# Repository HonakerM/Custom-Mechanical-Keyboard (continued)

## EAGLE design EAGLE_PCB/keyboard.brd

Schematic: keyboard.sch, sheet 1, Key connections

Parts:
0, 1, 2, 3, 4, 5, 6, 7, 8, 9: KEYSWITCH-RGBSMDLED-ALPSMX-1U-SMDRGB; ALPSMX-1U-SMDRGB
A: KEYSWITCH-RGBSMDLED-ALPSMX-1U-SMDRGB; ALPSMX-1U-SMDRGB
ALT, ALT2: KEYSWITCH-RGBSMDLED-ALPSMX-1U-SMDRGB; ALPSMX-1U-SMDRGB
B: KEYSWITCH-RGBSMDLED-ALPSMX-1U-SMDRGB; ALPSMX-1U-SMDRGB
BACKSLASH: KEYSWITCH-RGBSMDLED-ALPSMX-1U-SMDRGB; ALPSMX-1U-SMDRGB
BACKSONG: KEYSWITCH-RGBSMDLED-ALPSMX-1U-SMDRGB; ALPSMX-1U-SMDRGB
BACKSPACE: KEYSWITCH-RGBSMDLED-ALPSMX-2U-SMDRGB; ALPSMX-2U-SMDRGB
BACKSPACE_1: KEYSWITCH-RGBSMDLED-ALPSMX-1U-SMDRGB; ALPSMX-1U-SMDRGB
C: KEYSWITCH-RGBSMDLED-ALPSMX-1U-SMDRGB; ALPSMX-1U-SMDRGB
CAPSLOCK: KEYSWITCH-RGBSMDLED-ALPSMX-1U-SMDRGB; ALPSMX-1U-SMDRGB
COMMA: KEYSWITCH-RGBSMDLED-ALPSMX-1U-SMDRGB; ALPSMX-1U-SMDRGB
CTRL, CTRL1, CTRL2: KEYSWITCH-RGBSMDLED-ALPSMX-1U-SMDRGB; ALPSMX-1U-SMDRGB
D: KEYSWITCH-RGBSMDLED-ALPSMX-1U-SMDRGB; ALPSMX-1U-SMDRGB
D0, D1, D2, D3, D4, D5, D6, D7, D8, D9: DIODE-SOD-123; SOD-123
DA: DIODE-SOD-123; SOD-123
DALT, DALT2: DIODE-SOD-123; SOD-123
DASH: KEYSWITCH-RGBSMDLED-ALPSMX-1U-SMDRGB; ALPSMX-1U-SMDRGB
DB: DIODE-SOD-123; SOD-123
DBACKSLASH: DIODE-SOD-123; SOD-123
DBACKSONG: DIODE-SOD-123; SOD-123
DBACKSPACE: DIODE-SOD-123; SOD-123
DBACKSPACE_1: DIODE-SOD-123; SOD-123
DC: DIODE-SOD-123; SOD-123
DCAPSLOCK: DIODE-SOD-123; SOD-123
DCOMMA: DIODE-SOD-123; SOD-123
DCTRL, DCTRL2: DIODE-SOD-123; SOD-123
DD: DIODE-SOD-123; SOD-123
DDASH: DIODE-SOD-123; SOD-123
DDELETE, DDELETE2: DIODE-SOD-123; SOD-123
DDOWN: DIODE-SOD-123; SOD-123
DE: DIODE-SOD-123; SOD-123
DELETE: KEYSWITCH-RGBSMDLED-ALPSMX-1U-SMDRGB; ALPSMX-1U-SMDRGB
DEND: DIODE-SOD-123; SOD-123
DENTER, DENTER2: DIODE-SOD-123; SOD-123
DEQUAL, DEQUAL2: DIODE-SOD-123; SOD-123
DESC: DIODE-SOD-123; SOD-123
DF, DF1, DF2, DF3, DF4, DF5, DF6, DF7, DF8, DF9, DF10, DF11, DF12: DIODE-SOD-123; SOD-123
DG: DIODE-SOD-123; SOD-123
DGRAVE: DIODE-SOD-123; SOD-123
DH: DIODE-SOD-123; SOD-123
DHOME: DIODE-SOD-123; SOD-123
DI: DIODE-SOD-123; SOD-123
DINSERT: DIODE-SOD-123; SOD-123
DJ: DIODE-SOD-123; SOD-123
DK: DIODE-SOD-123; SOD-123
DKP_0, DKP_1, DKP_2, DKP_3, DKP_4, DKP_5, DKP_6, DKP_7, DKP_8, DKP_9, DKP_52, DKP_62: DIODE-SOD-123; SOD-123
DKP_ASTERISK: DIODE-SOD-123; SOD-123
DKP_DASH: DIODE-SOD-123; SOD-123
DKP_DEL: DIODE-SOD-123; SOD-123
DKP_SLASH: DIODE-SOD-123; SOD-123
DL: DIODE-SOD-123; SOD-123
DLBRACKET: DIODE-SOD-123; SOD-123
DLEFT: DIODE-SOD-123; SOD-123
DLOCK: DIODE-SOD-123; SOD-123
DM, DM1, DM2, DM3, DM4, DM5, DM6: DIODE-SOD-123; SOD-123
DMENU: DIODE-SOD-123; SOD-123
DN: DIODE-SOD-123; SOD-123
DNEXTSONG, DNEXTSONG1: DIODE-SOD-123; SOD-123
DNUMLOCK: DIODE-SOD-123; SOD-123
DO: DIODE-SOD-123; SOD-123
DOWN: KEYSWITCH-RGBSMDLED-ALPSMX-1U-SMDRGB; ALPSMX-1U-SMDRGB
DP: DIODE-SOD-123; SOD-123
DPAUSE: DIODE-SOD-123; SOD-123
DPAUSEPLAY: DIODE-SOD-123; SOD-123
DPERIOD: DIODE-SOD-123; SOD-123
DPGDN: DIODE-SOD-123; SOD-123
DPGUP: DIODE-SOD-123; SOD-123
DPRTSC: DIODE-SOD-123; SOD-123
DQ: DIODE-SOD-123; SOD-123
DQUOTE: DIODE-SOD-123; SOD-123
DR: DIODE-SOD-123; SOD-123
DRBRACKET: DIODE-SOD-123; SOD-123
DRIGHT: DIODE-SOD-123; SOD-123
DS: DIODE-SOD-123; SOD-123
DSCROLLLOCK: DIODE-SOD-123; SOD-123
DSEMICOLON: DIODE-SOD-123; SOD-123
DSHIFT, DSHIFT2: DIODE-SOD-123; SOD-123
DSLASH: DIODE-SOD-123; SOD-123
DSPACE: DIODE-SOD-123; SOD-123
DT: DIODE-SOD-123; SOD-123
DTAB: DIODE-SOD-123; SOD-123
DU: DIODE-SOD-123; SOD-123
DUNDERSCORE: DIODE-SOD-123; SOD-123
DUP: DIODE-SOD-123; SOD-123
DV: DIODE-SOD-123; SOD-123
DVOLUMEUP: DIODE-SOD-123; SOD-123
DVOLUMNEDOWN: DIODE-SOD-123; SOD-123
DW: DIODE-SOD-123; SOD-123
DWIN, DWIN2: DIODE-SOD-123; SOD-123
DX: DIODE-SOD-123; SOD-123
DY: DIODE-SOD-123; SOD-123
DZ: DIODE-SOD-123; SOD-123
E: KEYSWITCH-RGBSMDLED-ALPSMX-1U-SMDRGB; ALPSMX-1U-SMDRGB
END: KEYSWITCH-RGBSMDLED-ALPSMX-1U-SMDRGB; ALPSMX-1U-SMDRGB
ENTER: KEYSWITCH-RGBSMDLED-ALPSMX-2U-SMDRGB; ALPSMX-2U-SMDRGB
ENTER2: KEYSWITCH-RGBSMDLED-ALPSMX-2U-SMDRGB-ROTATED; ALPSMX-2U-SMDRGB-ROTATED
EQUAL: KEYSWITCH-RGBSMDLED-ALPSMX-1U-SMDRGB; ALPSMX-1U-SMDRGB
ESC: KEYSWITCH-RGBSMDLED-ALPSMX-1U-SMDRGB; ALPSMX-1U-SMDRGB
F, F1, F2, F3, F4, F5, F6, F7, F8, F9, F10, F11, F12: KEYSWITCH-RGBSMDLED-ALPSMX-1U-SMDRGB; ALPSMX-1U-SMDRGB
G: KEYSWITCH-RGBSMDLED-ALPSMX-1U-SMDRGB; ALPSMX-1U-SMDRGB
GRAVE: KEYSWITCH-RGBSMDLED-ALPSMX-1U-SMDRGB; ALPSMX-1U-SMDRGB
H: KEYSWITCH-RGBSMDLED-ALPSMX-1U-SMDRGB; ALPSMX-1U-SMDRGB
HOME: KEYSWITCH-RGBSMDLED-ALPSMX-1U-SMDRGB; ALPSMX-1U-SMDRGB
I: KEYSWITCH-RGBSMDLED-ALPSMX-1U-SMDRGB; ALPSMX-1U-SMDRGB
INSERT: KEYSWITCH-RGBSMDLED-ALPSMX-1U-SMDRGB; ALPSMX-1U-SMDRGB
J: KEYSWITCH-RGBSMDLED-ALPSMX-1U-SMDRGB; ALPSMX-1U-SMDRGB
K: KEYSWITCH-RGBSMDLED-ALPSMX-1U-SMDRGB; ALPSMX-1U-SMDRGB
KP_0: KEYSWITCH-RGBSMDLED-ALPSMX-2U-SMDRGB; ALPSMX-2U-SMDRGB
KP_1, KP_2, KP_3, KP_4, KP_5, KP_6, KP_7, KP_8, KP_9, KP_52, KP_62: KEYSWITCH-RGBSMDLED-ALPSMX-1U-SMDRGB; ALPSMX-1U-SMDRGB
KP_ASTERISK: KEYSWITCH-RGBSMDLED-ALPSMX-1U-SMDRGB; ALPSMX-1U-SMDRGB
KP_DASH: KEYSWITCH-RGBSMDLED-ALPSMX-1U-SMDRGB; ALPSMX-1U-SMDRGB
KP_DEL: KEYSWITCH-RGBSMDLED-ALPSMX-1U-SMDRGB; ALPSMX-1U-SMDRGB
KP_DELETE2: KEYSWITCH-RGBSMDLED-ALPSMX-1U-SMDRGB; ALPSMX-1U-SMDRGB
KP_SLASH: KEYSWITCH-RGBSMDLED-ALPSMX-1U-SMDRGB; ALPSMX-1U-SMDRGB
L: KEYSWITCH-RGBSMDLED-ALPSMX-1U-SMDRGB; ALPSMX-1U-SMDRGB
LBRACKET: KEYSWITCH-RGBSMDLED-ALPSMX-1U-SMDRGB; ALPSMX-1U-SMDRGB
LEFT: KEYSWITCH-RGBSMDLED-ALPSMX-1U-SMDRGB; ALPSMX-1U-SMDRGB
LOCK: KEYSWITCH-RGBSMDLED-ALPSMX-1U-SMDRGB; ALPSMX-1U-SMDRGB
M, M2, M3, M4, M5, M6: KEYSWITCH-RGBSMDLED-ALPSMX-1U-SMDRGB; ALPSMX-1U-SMDRGB
MENU: KEYSWITCH-RGBSMDLED-ALPSMX-1U-SMDRGB; ALPSMX-1U-SMDRGB
N: KEYSWITCH-RGBSMDLED-ALPSMX-1U-SMDRGB; ALPSMX-1U-SMDRGB
NEXTSONG: KEYSWITCH-RGBSMDLED-ALPSMX-1U-SMDRGB; ALPSMX-1U-SMDRGB
NUMLOCK: KEYSWITCH-RGBSMDLED-ALPSMX-1U-SMDRGB; ALPSMX-1U-SMDRGB
O: KEYSWITCH-RGBSMDLED-ALPSMX-1U-SMDRGB; ALPSMX-1U-SMDRGB
P: KEYSWITCH-RGBSMDLED-ALPSMX-1U-SMDRGB; ALPSMX-1U-SMDRGB
PAUSE: KEYSWITCH-RGBSMDLED-ALPSMX-1U-SMDRGB; ALPSMX-1U-SMDRGB
PAUSEPLAY: KEYSWITCH-RGBSMDLED-ALPSMX-1U-SMDRGB; ALPSMX-1U-SMDRGB
PERIOD: KEYSWITCH-RGBSMDLED-ALPSMX-1U-SMDRGB; ALPSMX-1U-SMDRGB
PGDN: KEYSWITCH-RGBSMDLED-ALPSMX-1U-SMDRGB; ALPSMX-1U-SMDRGB
PGUP: KEYSWITCH-RGBSMDLED-ALPSMX-1U-SMDRGB; ALPSMX-1U-SMDRGB
PLUS2: KEYSWITCH-RGBSMDLED-ALPSMX-2U-SMDRGB-ROTATED; ALPSMX-2U-SMDRGB-ROTATED
PRTSC: KEYSWITCH-RGBSMDLED-ALPSMX-1U-SMDRGB; ALPSMX-1U-SMDRGB
Q: KEYSWITCH-RGBSMDLED-ALPSMX-1U-SMDRGB; ALPSMX-1U-SMDRGB
QUOTE: KEYSWITCH-RGBSMDLED-ALPSMX-1U-SMDRGB; ALPSMX-1U-SMDRGB
R: KEYSWITCH-RGBSMDLED-ALPSMX-1U-SMDRGB; ALPSMX-1U-SMDRGB
RANDSONG: KEYSWITCH-RGBSMDLED-ALPSMX-1U-SMDRGB; ALPSMX-1U-SMDRGB
RBRACKET: KEYSWITCH-RGBSMDLED-ALPSMX-1U-SMDRGB; ALPSMX-1U-SMDRGB
RIGHT: KEYSWITCH-RGBSMDLED-ALPSMX-1U-SMDRGB; ALPSMX-1U-SMDRGB
S: KEYSWITCH-RGBSMDLED-ALPSMX-1U-SMDRGB; ALPSMX-1U-SMDRGB
SCROLLLOCK: KEYSWITCH-RGBSMDLED-ALPSMX-1U-SMDRGB; ALPSMX-1U-SMDRGB
SEMICOLON: KEYSWITCH-RGBSMDLED-ALPSMX-1U-SMDRGB; ALPSMX-1U-SMDRGB
SHIFT, SHIFT2: KEYSWITCH-RGBSMDLED-ALPSMX-2U-SMDRGB; ALPSMX-2U-SMDRGB
SLASH: KEYSWITCH-RGBSMDLED-ALPSMX-1U-SMDRGB; ALPSMX-1U-SMDRGB
SPACE: KEYSWITCH-RGBSMDLED-ALPSMX-6.25U-SMDRGB; ALPSMX-6.25U-SMDRGB
T: KEYSWITCH-RGBSMDLED-ALPSMX-1U-SMDRGB; ALPSMX-1U-SMDRGB
TAB: KEYSWITCH-RGBSMDLED-ALPSMX-1U-SMDRGB; ALPSMX-1U-SMDRGB
U: KEYSWITCH-RGBSMDLED-ALPSMX-1U-SMDRGB; ALPSMX-1U-SMDRGB
UNDERSCORE: KEYSWITCH-RGBSMDLED-ALPSMX-1U-SMDRGB; ALPSMX-1U-SMDRGB
UP: KEYSWITCH-RGBSMDLED-ALPSMX-1U-SMDRGB; ALPSMX-1U-SMDRGB
V: KEYSWITCH-RGBSMDLED-ALPSMX-1U-SMDRGB; ALPSMX-1U-SMDRGB
VOLUMEUP: KEYSWITCH-RGBSMDLED-ALPSMX-1U-SMDRGB; ALPSMX-1U-SMDRGB
VOLUMNEDOWN: KEYSWITCH-RGBSMDLED-ALPSMX-1U-SMDRGB; ALPSMX-1U-SMDRGB
W: KEYSWITCH-RGBSMDLED-ALPSMX-1U-SMDRGB; ALPSMX-1U-SMDRGB
WIN, WIN2: KEYSWITCH-RGBSMDLED-ALPSMX-1U-SMDRGB; ALPSMX-1U-SMDRGB
X: KEYSWITCH-RGBSMDLED-ALPSMX-1U-SMDRGB; ALPSMX-1U-SMDRGB
Y: KEYSWITCH-RGBSMDLED-ALPSMX-1U-SMDRGB; ALPSMX-1U-SMDRGB
Z: KEYSWITCH-RGBSMDLED-ALPSMX-1U-SMDRGB; ALPSMX-1U-SMDRGB

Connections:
+5V: 0.VDD (VCC), 1.VDD (VCC), 2.VDD (VCC), 3.VDD (VCC), 4.VDD (VCC), 5.VDD (VCC), 6.VDD (VCC), 7.VDD (VCC), 8.VDD (VCC), 9.VDD (VCC), A.VDD (VCC), ALT.VDD (VCC), ALT2.VDD (VCC), B.VDD (VCC), BACKSLASH.VDD (VCC), BACKSONG.VDD (VCC), BACKSPACE.VDD (VCC), BACKSPACE_1.VDD (VCC), C.VDD (VCC), CAPSLOCK.VDD (VCC), COMMA.VDD (VCC), CTRL.VDD (VCC), CTRL1.VDD (VCC), D.VDD (VCC), DASH.VDD (VCC), DELETE.VDD (VCC), DOWN.VDD (VCC), E.VDD (VCC), END.VDD (VCC), ENTER2.DOUT (VCC), EQUAL.VDD (VCC), ESC.VDD (VCC), F.VDD (VCC), F1.VDD (VCC), F2.VDD (VCC), F3.VDD (VCC), F4.VDD (VCC), F5.VDD (VCC), F6.VDD (VCC), F7.VDD (VCC), F8.VDD (VCC), F9.VDD (VCC), F10.VDD (VCC), F11.VDD (VCC), F12.VDD (VCC), G.VDD (VCC), GRAVE.VDD (VCC), H.VDD (VCC), HOME.VDD (VCC), I.VDD (VCC), INSERT.VDD (VCC), J.VDD (VCC), K.VDD (VCC), KP_0.VDD (VCC), KP_1.VDD (VCC), KP_2.VDD (VCC), KP_3.VDD (VCC), KP_4.VDD (VCC), KP_5.VDD (VCC), KP_6.VDD (VCC), KP_7.VDD (VCC), KP_8.VDD (VCC), KP_9.VDD (VCC), KP_62.VDD (VCC), KP_ASTERISK.VDD (VCC), KP_DASH.VDD (VCC), KP_DEL.VDD (VCC), KP_DELETE2.VDD (VCC), KP_SLASH.VDD (VCC), L.VDD (VCC), LBRACKET.VDD (VCC), LEFT.VDD (VCC), LOCK.VDD (VCC), M.VDD (VCC), M2.VDD (VCC), M3.VDD (VCC), M4.VDD (VCC), M5.VDD (VCC), M6.VDD (VCC), MENU.VDD (VCC), N.VDD (VCC), NEXTSONG.VDD (VCC), NUMLOCK.VDD (VCC), O.VDD (VCC), P.VDD (VCC), PAUSE.VDD (VCC), PAUSEPLAY.VDD (VCC), PERIOD.VDD (VCC), PGDN.VDD (VCC), PGUP.VDD (VCC), PLUS2.DOUT (VCC), PRTSC.VDD (VCC), Q.VDD (VCC), QUOTE.VDD (VCC), R.VDD (VCC), RANDSONG.VDD (VCC), RBRACKET.VDD (VCC), RIGHT.VDD (VCC), S.VDD (VCC), SCROLLLOCK.VDD (VCC), SEMICOLON.VDD (VCC), SHIFT.VDD (VCC), SHIFT2.VDD (VCC), SLASH.VDD (VCC), SPACE.DIN (VCC), T.VDD (VCC), TAB.VDD (VCC), U.VDD (VCC), UNDERSCORE.VDD (VCC), UP.VDD (VCC), V.VDD (VCC), VOLUMEUP.VDD (VCC), VOLUMNEDOWN.VDD (VCC), W.VDD (VCC), WIN.VDD (VCC), WIN2.VDD (VCC), X.VDD (VCC), Y.VDD (VCC), Z.VDD (VCC); also elsewhere on the board
COL2: CTRL1.ALPS1 (P0), CTRL1.MX1 (P0), M2.ALPS1 (P0), M2.MX1 (P0), M3.ALPS1 (P0), M3.MX1 (P0), M4.ALPS1 (P0), M4.MX1 (P0), M5.ALPS1 (P0), M5.MX1 (P0), M6.ALPS1 (P0), M6.MX1 (P0); also elsewhere on the board
COL3: CAPSLOCK.ALPS1 (P0), CAPSLOCK.MX1 (P0), CTRL.ALPS1 (P0), CTRL.MX1 (P0), ESC.ALPS1 (P0), ESC.MX1 (P0), GRAVE.ALPS1 (P0), GRAVE.MX1 (P0), SHIFT.ALPS1 (P0), SHIFT.MX1 (P0), TAB.ALPS1 (P0), TAB.MX1 (P0); also elsewhere on the board
COL4: 1.ALPS1 (P0), 1.MX1 (P0), A.ALPS1 (P0), A.MX1 (P0), F1.ALPS1 (P0), F1.MX1 (P0), Q.ALPS1 (P0), Q.MX1 (P0), WIN.ALPS1 (P0), WIN.MX1 (P0), Z.ALPS1 (P0), Z.MX1 (P0); also elsewhere on the board
COL5: 2.ALPS1 (P0), 2.MX1 (P0), ALT.ALPS1 (P0), ALT.MX1 (P0), F2.ALPS1 (P0), F2.MX1 (P0), S.ALPS1 (P0), S.MX1 (P0), W.ALPS1 (P0), W.MX1 (P0), X.ALPS1 (P0), X.MX1 (P0); also elsewhere on the board
COL6: 3.ALPS1 (P0), 3.MX1 (P0), C.ALPS1 (P0), C.MX1 (P0), D.ALPS1 (P0), D.MX1 (P0), E.ALPS1 (P0), E.MX1 (P0), F3.ALPS1 (P0), F3.MX1 (P0); also elsewhere on the board
COL7: 4.ALPS1 (P0), 4.MX1 (P0), F.ALPS1 (P0), F.MX1 (P0), F4.ALPS1 (P0), F4.MX1 (P0), R.ALPS1 (P0), R.MX1 (P0), V.ALPS1 (P0), V.MX1 (P0); also elsewhere on the board
COL8: 5.ALPS1 (P0), 5.MX1 (P0), B.ALPS1 (P0), B.MX1 (P0), F5.ALPS1 (P0), F5.MX1 (P0), G.ALPS1 (P0), G.MX1 (P0), SPACE.ALPS1 (P0), SPACE.MX1 (P0), T.ALPS1 (P0), T.MX1 (P0); also elsewhere on the board
COL9: 6.ALPS1 (P0), 6.MX1 (P0), F6.ALPS1 (P0), F6.MX1 (P0), H.ALPS1 (P0), H.MX1 (P0), N.ALPS1 (P0), N.MX1 (P0), Y.ALPS1 (P0), Y.MX1 (P0); also elsewhere on the board
COL10: 7.ALPS1 (P0), 7.MX1 (P0), F7.ALPS1 (P0), F7.MX1 (P0), J.ALPS1 (P0), J.MX1 (P0), M.ALPS1 (P0), M.MX1 (P0), U.ALPS1 (P0), U.MX1 (P0); also elsewhere on the board
COL11: 8.ALPS1 (P0), 8.MX1 (P0), COMMA.ALPS1 (P0), COMMA.MX1 (P0), F8.ALPS1 (P0), F8.MX1 (P0), I.ALPS1 (P0), I.MX1 (P0), K.ALPS1 (P0), K.MX1 (P0); also elsewhere on the board
COL12: 9.ALPS1 (P0), 9.MX1 (P0), ALT2.ALPS1 (P0), ALT2.MX1 (P0), F9.ALPS1 (P0), F9.MX1 (P0), L.ALPS1 (P0), L.MX1 (P0), O.ALPS1 (P0), O.MX1 (P0), PERIOD.ALPS1 (P0), PERIOD.MX1 (P0); also elsewhere on the board
COL13: 0.ALPS1 (P0), 0.MX1 (P0), F10.ALPS1 (P0), F10.MX1 (P0), P.ALPS1 (P0), P.MX1 (P0), SEMICOLON.ALPS1 (P0), SEMICOLON.MX1 (P0), SLASH.ALPS1 (P0), SLASH.MX1 (P0), WIN2.ALPS1 (P0), WIN2.MX1 (P0); also elsewhere on the board
COL14: DASH.ALPS1 (P0), DASH.MX1 (P0), F11.ALPS1 (P0), F11.MX1 (P0), LBRACKET.ALPS1 (P0), LBRACKET.MX1 (P0), MENU.ALPS1 (P0), MENU.MX1 (P0), QUOTE.ALPS1 (P0), QUOTE.MX1 (P0); also elsewhere on the board
COL15: EQUAL.ALPS1 (P0), EQUAL.MX1 (P0), F12.ALPS1 (P0), F12.MX1 (P0), RBRACKET.ALPS1 (P0), RBRACKET.MX1 (P0); also elsewhere on the board
COL16: VOLUMEUP.ALPS1 (P0), VOLUMEUP.MX1 (P0); also elsewhere on the board
COL17: BACKSLASH.ALPS1 (P0), BACKSLASH.MX1 (P0), BACKSPACE.ALPS1 (P0), BACKSPACE.MX1 (P0), CTRL2.ALPS1 (P0), CTRL2.MX1 (P0), ENTER.ALPS1 (P0), ENTER.MX1 (P0), SHIFT2.ALPS1 (P0), SHIFT2.MX1 (P0), VOLUMNEDOWN.ALPS1 (P0), VOLUMNEDOWN.MX1 (P0); also elsewhere on the board
COL18: DELETE.ALPS1 (P0), DELETE.MX1 (P0), INSERT.ALPS1 (P0), INSERT.MX1 (P0), LEFT.ALPS1 (P0), LEFT.MX1 (P0), PRTSC.ALPS1 (P0), PRTSC.MX1 (P0); also elsewhere on the board
COL19: DOWN.ALPS1 (P0), DOWN.MX1 (P0), END.ALPS1 (P0), END.MX1 (P0), HOME.ALPS1 (P0), HOME.MX1 (P0), SCROLLLOCK.ALPS1 (P0), SCROLLLOCK.MX1 (P0), UP.ALPS1 (P0), UP.MX1 (P0); also elsewhere on the board
COL20: PAUSE.ALPS1 (P0), PAUSE.MX1 (P0), PGDN.ALPS1 (P0), PGDN.MX1 (P0), PGUP.ALPS1 (P0), PGUP.MX1 (P0), RIGHT.ALPS1 (P0), RIGHT.MX1 (P0); also elsewhere on the board
COL21: BACKSONG.ALPS1 (P0), BACKSONG.MX1 (P0), KP_0.ALPS1 (P0), KP_0.MX1 (P0), KP_1.ALPS1 (P0), KP_1.MX1 (P0), KP_4.ALPS1 (P0), KP_4.MX1 (P0), KP_7.ALPS1 (P0), KP_7.MX1 (P0), NUMLOCK.ALPS1 (P0), NUMLOCK.MX1 (P0); also elsewhere on the board
COL22: KP_2.ALPS1 (P0), KP_2.MX1 (P0), KP_8.ALPS1 (P0), KP_8.MX1 (P0), KP_52.ALPS1 (P0), KP_52.MX1 (P0), KP_SLASH.ALPS1 (P0), KP_SLASH.MX1 (P0), PAUSEPLAY.ALPS1 (P0), PAUSEPLAY.MX1 (P0); also elsewhere on the board
COL23: KP_3.ALPS1 (P0), KP_3.MX1 (P0), KP_6.ALPS1 (P0), KP_6.MX1 (P0), KP_9.ALPS1 (P0), KP_9.MX1 (P0), KP_ASTERISK.ALPS1 (P0), KP_ASTERISK.MX1 (P0), KP_DEL.ALPS1 (P0), KP_DEL.MX1 (P0), NEXTSONG.ALPS1 (P0), NEXTSONG.MX1 (P0); also elsewhere on the board
COL24: ENTER2.ALPS1 (P0), ENTER2.MX1 (P0), KP_DASH.ALPS1 (P0), KP_DASH.MX1 (P0), PLUS2.ALPS1 (P0), PLUS2.MX1 (P0), RANDSONG.ALPS1 (P0), RANDSONG.MX1 (P0); also elsewhere on the board
COL25: BACKSPACE_1.ALPS1 (P0), BACKSPACE_1.MX1 (P0), KP_5.ALPS1 (P0), KP_5.MX1 (P0), KP_62.ALPS1 (P0), KP_62.MX1 (P0), KP_DELETE2.ALPS1 (P0), KP_DELETE2.MX1 (P0), LOCK.ALPS1 (P0), LOCK.MX1 (P0), UNDERSCORE.ALPS1 (P0), UNDERSCORE.MX1 (P0); also elsewhere on the board
GND: 0.VSS (GND), 1.VSS (GND), 2.VSS (GND), 3.VSS (GND), 4.VSS (GND), 5.VSS (GND), 6.VSS (GND), 7.VSS (GND), 8.VSS (GND), 9.VSS (GND), A.VSS (GND), ALT.VSS (GND), ALT2.VSS (GND), B.VSS (GND), BACKSLASH.VSS (GND), BACKSONG.VSS (GND), BACKSPACE.VSS (GND), BACKSPACE_1.VSS (GND), C.VSS (GND), CAPSLOCK.VSS (GND), COMMA.VSS (GND), CTRL.VSS (GND), CTRL1.VSS (GND), CTRL2.VSS (GND), D.VSS (GND), DASH.VSS (GND), DELETE.VSS (GND), DOWN.VSS (GND), E.VSS (GND), END.VSS (GND), ENTER.VSS (GND), ENTER2.VDD (GND), EQUAL.VSS (GND), ESC.VSS (GND), F.VSS (GND), F1.VSS (GND), F2.VSS (GND), F3.VSS (GND), F4.VSS (GND), F5.VSS (GND), F6.VSS (GND), F7.VSS (GND), F8.VSS (GND), F9.VSS (GND), F10.VSS (GND), F11.VSS (GND), F12.VSS (GND), G.VSS (GND), GRAVE.VSS (GND), H.VSS (GND), HOME.VSS (GND), I.VSS (GND), INSERT.VSS (GND), J.VSS (GND), K.VSS (GND), KP_0.VSS (GND), KP_1.VSS (GND), KP_2.VSS (GND), KP_3.VSS (GND), KP_4.VSS (GND), KP_5.VSS (GND), KP_6.VSS (GND), KP_7.VSS (GND), KP_8.VSS (GND), KP_9.VSS (GND), KP_52.VSS (GND), KP_62.VSS (GND), KP_ASTERISK.VSS (GND), KP_DASH.VSS (GND), KP_DEL.VSS (GND), KP_DELETE2.VSS (GND), KP_SLASH.VSS (GND), L.VSS (GND), LBRACKET.VSS (GND), LEFT.VSS (GND), LOCK.VSS (GND), M.VSS (GND), M2.VSS (GND), M3.VSS (GND), M4.VSS (GND), M5.VSS (GND), M6.VSS (GND), MENU.VSS (GND), N.VSS (GND), NEXTSONG.VSS (GND), NUMLOCK.VSS (GND), O.VSS (GND), P.VSS (GND), PAUSE.VSS (GND), PAUSEPLAY.VSS (GND), PERIOD.VSS (GND), PGDN.VSS (GND), PGUP.VSS (GND), PLUS2.VDD (GND), PRTSC.VSS (GND), Q.VSS (GND), QUOTE.VSS (GND), R.VSS (GND), RANDSONG.VSS (GND), RBRACKET.VSS (GND), RIGHT.VSS (GND), S.VSS (GND), SCROLLLOCK.VSS (GND), SEMICOLON.VSS (GND), SHIFT.VSS (GND), SHIFT2.VSS (GND), SLASH.VSS (GND), SPACE.VDD (GND), T.VSS (GND), TAB.VSS (GND), U.VSS (GND), UNDERSCORE.VSS (GND), UP.VSS (GND), V.VSS (GND), VOLUMEUP.VSS (GND), VOLUMNEDOWN.VSS (GND), W.VSS (GND), WIN.VSS (GND), WIN2.VSS (GND), X.VSS (GND), Y.VSS (GND), Z.VSS (GND); also elsewhere on the board
LED1: M6.DIN (DI); also elsewhere on the board
LED2: M5.DIN (DI); also elsewhere on the board
LED3: M4.DIN (DI); also elsewhere on the board
LED4: M3.DIN (DI); also elsewhere on the board
LED5: M2.DIN (DI); also elsewhere on the board
LED6: CTRL1.DIN (DI); also elsewhere on the board
unnamed: DESC.A, ESC.ALPS2 (P1), ESC.MX2 (P1)
unnamed: DF1.A, F1.ALPS2 (P1), F1.MX2 (P1)
unnamed: DF2.A, F2.ALPS2 (P1), F2.MX2 (P1)
unnamed: DF3.A, F3.ALPS2 (P1), F3.MX2 (P1)
unnamed: DF4.A, F4.ALPS2 (P1), F4.MX2 (P1)
unnamed: DF5.A, F5.ALPS2 (P1), F5.MX2 (P1)
unnamed: DF6.A, F6.ALPS2 (P1), F6.MX2 (P1)
unnamed: DF7.A, F7.ALPS2 (P1), F7.MX2 (P1)
unnamed: DF8.A, F8.ALPS2 (P1), F8.MX2 (P1)
unnamed: DF9.A, F9.ALPS2 (P1), F9.MX2 (P1)
unnamed: DF10.A, F10.ALPS2 (P1), F10.MX2 (P1)
unnamed: DF11.A, F11.ALPS2 (P1), F11.MX2 (P1)
unnamed: DF12.A, F12.ALPS2 (P1), F12.MX2 (P1)
unnamed: DVOLUMEUP.A, VOLUMEUP.ALPS2 (P1), VOLUMEUP.MX2 (P1)
unnamed: DVOLUMNEDOWN.A, VOLUMNEDOWN.ALPS2 (P1), VOLUMNEDOWN.MX2 (P1)
unnamed: DPRTSC.A, PRTSC.ALPS2 (P1), PRTSC.MX2 (P1)
unnamed: DSCROLLLOCK.A, SCROLLLOCK.ALPS2 (P1), SCROLLLOCK.MX2 (P1)
unnamed: DPAUSE.A, PAUSE.ALPS2 (P1), PAUSE.MX2 (P1)
unnamed: BACKSONG.ALPS2 (P1), BACKSONG.MX2 (P1), DBACKSONG.A
unnamed: DPAUSEPLAY.A, PAUSEPLAY.ALPS2 (P1), PAUSEPLAY.MX2 (P1)
unnamed: DNEXTSONG.A, NEXTSONG.ALPS2 (P1), NEXTSONG.MX2 (P1)
unnamed: DLOCK.A, LOCK.ALPS2 (P1), LOCK.MX2 (P1)
unnamed: DGRAVE.A, GRAVE.ALPS2 (P1), GRAVE.MX2 (P1)
unnamed: 1.ALPS2 (P1), 1.MX2 (P1), D1.A
unnamed: 2.ALPS2 (P1), 2.MX2 (P1), D2.A
unnamed: 3.ALPS2 (P1), 3.MX2 (P1), D3.A
unnamed: 4.ALPS2 (P1), 4.MX2 (P1), D4.A
unnamed: 5.ALPS2 (P1), 5.MX2 (P1), D5.A
unnamed: 6.ALPS2 (P1), 6.MX2 (P1), D6.A
unnamed: 7.ALPS2 (P1), 7.MX2 (P1), D7.A
unnamed: 8.ALPS2 (P1), 8.MX2 (P1), D8.A
unnamed: 9.ALPS2 (P1), 9.MX2 (P1), D9.A
unnamed: 0.ALPS2 (P1), 0.MX2 (P1), D0.A
unnamed: DASH.ALPS2 (P1), DASH.MX2 (P1), DDASH.A
unnamed: DEQUAL.A, EQUAL.ALPS2 (P1), EQUAL.MX2 (P1)
unnamed: BACKSPACE.ALPS2 (P1), BACKSPACE.MX2 (P1), DBACKSPACE.A
unnamed: DINSERT.A, INSERT.ALPS2 (P1), INSERT.MX2 (P1)
unnamed: DHOME.A, HOME.ALPS2 (P1), HOME.MX2 (P1)
unnamed: DPGUP.A, PGUP.ALPS2 (P1), PGUP.MX2 (P1)
unnamed: DNUMLOCK.A, NUMLOCK.ALPS2 (P1), NUMLOCK.MX2 (P1)
unnamed: DKP_SLASH.A, KP_SLASH.ALPS2 (P1), KP_SLASH.MX2 (P1)
unnamed: DKP_ASTERISK.A, KP_ASTERISK.ALPS2 (P1), KP_ASTERISK.MX2 (P1)
unnamed: DKP_DASH.A, KP_DASH.ALPS2 (P1), KP_DASH.MX2 (P1)
unnamed: DUNDERSCORE.A, UNDERSCORE.ALPS2 (P1), UNDERSCORE.MX2 (P1)
unnamed: DTAB.A, TAB.ALPS2 (P1), TAB.MX2 (P1)
unnamed: DQ.A, Q.ALPS2 (P1), Q.MX2 (P1)
unnamed: DW.A, W.ALPS2 (P1), W.MX2 (P1)
unnamed: DE.A, E.ALPS2 (P1), E.MX2 (P1)
unnamed: DR.A, R.ALPS2 (P1), R.MX2 (P1)
unnamed: DT.A, T.ALPS2 (P1), T.MX2 (P1)
unnamed: DY.A, Y.ALPS2 (P1), Y.MX2 (P1)
unnamed: DU.A, U.ALPS2 (P1), U.MX2 (P1)
unnamed: DI.A, I.ALPS2 (P1), I.MX2 (P1)
unnamed: DO.A, O.ALPS2 (P1), O.MX2 (P1)
unnamed: DP.A, P.ALPS2 (P1), P.MX2 (P1)
unnamed: DLBRACKET.A, LBRACKET.ALPS2 (P1), LBRACKET.MX2 (P1)
unnamed: DRBRACKET.A, RBRACKET.ALPS2 (P1), RBRACKET.MX2 (P1)
unnamed: BACKSLASH.ALPS2 (P1), BACKSLASH.MX2 (P1), DBACKSLASH.A
unnamed: DDELETE.A, DELETE.ALPS2 (P1), DELETE.MX2 (P1)
unnamed: DEND.A, END.ALPS2 (P1), END.MX2 (P1)
unnamed: DPGDN.A, PGDN.ALPS2 (P1), PGDN.MX2 (P1)
unnamed: DKP_7.A, KP_7.ALPS2 (P1), KP_7.MX2 (P1)
unnamed: DKP_8.A, KP_8.ALPS2 (P1), KP_8.MX2 (P1)
unnamed: DKP_9.A, KP_9.ALPS2 (P1), KP_9.MX2 (P1)
unnamed: DEQUAL2.A, PLUS2.ALPS2 (P1), PLUS2.MX2 (P1)
unnamed: DKP_5.A, KP_5.ALPS2 (P1), KP_5.MX2 (P1)
unnamed: CAPSLOCK.ALPS2 (P1), CAPSLOCK.MX2 (P1), DCAPSLOCK.A
unnamed: A.ALPS2 (P1), A.MX2 (P1), DA.A
unnamed: DS.A, S.ALPS2 (P1), S.MX2 (P1)
unnamed: D.ALPS2 (P1), D.MX2 (P1), DD.A
unnamed: DF.A, F.ALPS2 (P1), F.MX2 (P1)
unnamed: DG.A, G.ALPS2 (P1), G.MX2 (P1)
unnamed: DH.A, H.ALPS2 (P1), H.MX2 (P1)
unnamed: DJ.A, J.ALPS2 (P1), J.MX2 (P1)
unnamed: DK.A, K.ALPS2 (P1), K.MX2 (P1)
unnamed: DL.A, L.ALPS2 (P1), L.MX2 (P1)
unnamed: DSEMICOLON.A, SEMICOLON.ALPS2 (P1), SEMICOLON.MX2 (P1)
unnamed: DQUOTE.A, QUOTE.ALPS2 (P1), QUOTE.MX2 (P1)
unnamed: DENTER.A, ENTER.ALPS2 (P1), ENTER.MX2 (P1)
unnamed: DKP_4.A, KP_4.ALPS2 (P1), KP_4.MX2 (P1)
unnamed: DKP_52.A, KP_52.ALPS2 (P1), KP_52.MX2 (P1)
unnamed: DKP_6.A, KP_6.ALPS2 (P1), KP_6.MX2 (P1)
unnamed: DKP_62.A, KP_62.ALPS2 (P1), KP_62.MX2 (P1)
unnamed: DSHIFT.A, SHIFT.ALPS2 (P1), SHIFT.MX2 (P1)
unnamed: DZ.A, Z.ALPS2 (P1), Z.MX2 (P1)
unnamed: DX.A, X.ALPS2 (P1), X.MX2 (P1)
unnamed: C.ALPS2 (P1), C.MX2 (P1), DC.A
unnamed: DV.A, V.ALPS2 (P1), V.MX2 (P1)
unnamed: B.ALPS2 (P1), B.MX2 (P1), DB.A
unnamed: DN.A, N.ALPS2 (P1), N.MX2 (P1)
unnamed: DM.A, M.ALPS2 (P1), M.MX2 (P1)
unnamed: COMMA.ALPS2 (P1), COMMA.MX2 (P1), DCOMMA.A
unnamed: DPERIOD.A, PERIOD.ALPS2 (P1), PERIOD.MX2 (P1)
unnamed: DSLASH.A, SLASH.ALPS2 (P1), SLASH.MX2 (P1)
unnamed: DSHIFT2.A, SHIFT2.ALPS2 (P1), SHIFT2.MX2 (P1)
unnamed: DUP.A, UP.ALPS2 (P1), UP.MX2 (P1)
unnamed: DKP_1.A, KP_1.ALPS2 (P1), KP_1.MX2 (P1)
unnamed: DKP_2.A, KP_2.ALPS2 (P1), KP_2.MX2 (P1)
unnamed: DKP_3.A, KP_3.ALPS2 (P1), KP_3.MX2 (P1)
unnamed: DENTER2.A, ENTER2.ALPS2 (P1), ENTER2.MX2 (P1)
unnamed: DDELETE2.A, KP_DELETE2.ALPS2 (P1), KP_DELETE2.MX2 (P1)
unnamed: CTRL.ALPS2 (P1), CTRL.MX2 (P1), DCTRL.A
unnamed: DWIN.A, WIN.ALPS2 (P1), WIN.MX2 (P1)
unnamed: ALT.ALPS2 (P1), ALT.MX2 (P1), DALT.A
unnamed: DSPACE.A, SPACE.ALPS2 (P1), SPACE.MX2 (P1)
unnamed: ALT2.ALPS2 (P1), ALT2.MX2 (P1), DALT2.A
unnamed: ESC.DIN (DI), M6.DOUT (DO)
unnamed: DMENU.A, MENU.ALPS2 (P1), MENU.MX2 (P1)
unnamed: CTRL2.ALPS2 (P1), CTRL2.MX2 (P1), DCTRL2.A
unnamed: DLEFT.A, LEFT.ALPS2 (P1), LEFT.MX2 (P1)
unnamed: DDOWN.A, DOWN.ALPS2 (P1), DOWN.MX2 (P1)
unnamed: DRIGHT.A, RIGHT.ALPS2 (P1), RIGHT.MX2 (P1)
unnamed: DKP_0.A, KP_0.ALPS2 (P1), KP_0.MX2 (P1)
unnamed: DKP_DEL.A, KP_DEL.ALPS2 (P1), KP_DEL.MX2 (P1)
unnamed: BACKSPACE_1.ALPS2 (P1), BACKSPACE_1.MX2 (P1), DBACKSPACE_1.A
unnamed: BACKSPACE.DIN (DI), EQUAL.DOUT (DO)
unnamed: ESC.DOUT (DO), F1.DIN (DI)
unnamed: F1.DOUT (DO), F2.DIN (DI)
unnamed: DM6.A, M6.ALPS2 (P1), M6.MX2 (P1)
unnamed: F2.DOUT (DO), F3.DIN (DI)
unnamed: F3.DOUT (DO), F4.DIN (DI)
unnamed: F4.DOUT (DO), F5.DIN (DI)
unnamed: F5.DOUT (DO), F6.DIN (DI)
unnamed: DWIN2.A, WIN2.ALPS2 (P1), WIN2.MX2 (P1)
unnamed: DM2.A, M2.ALPS2 (P1), M2.MX2 (P1)
unnamed: DM5.A, M5.ALPS2 (P1), M5.MX2 (P1)
unnamed: DM4.A, M4.ALPS2 (P1), M4.MX2 (P1)
unnamed: DM3.A, M3.ALPS2 (P1), M3.MX2 (P1)
unnamed: CTRL1.ALPS2 (P1), CTRL1.MX2 (P1), DM1.A
unnamed: DNEXTSONG1.A, RANDSONG.ALPS2 (P1), RANDSONG.MX2 (P1)
unnamed: F6.DOUT (DO), F7.DIN (DI)
unnamed: F7.DOUT (DO), F8.DIN (DI)
unnamed: F8.DOUT (DO), F9.DIN (DI)
unnamed: F9.DOUT (DO), F10.DIN (DI)
unnamed: F10.DOUT (DO), F11.DIN (DI)
unnamed: F11.DOUT (DO), F12.DIN (DI)
unnamed: F12.DOUT (DO), VOLUMEUP.DIN (DI)
unnamed: VOLUMEUP.DOUT (DO), VOLUMNEDOWN.DIN (DI)
unnamed: PRTSC.DIN (DI), VOLUMNEDOWN.DOUT (DO)
unnamed: PRTSC.DOUT (DO), SCROLLLOCK.DIN (DI)
unnamed: PAUSE.DIN (DI), SCROLLLOCK.DOUT (DO)
unnamed: BACKSONG.DIN (DI), PAUSE.DOUT (DO)
unnamed: BACKSONG.DOUT (DO), PAUSEPLAY.DIN (DI)
unnamed: NEXTSONG.DIN (DI), PAUSEPLAY.DOUT (DO)
unnamed: NEXTSONG.DOUT (DO), RANDSONG.DIN (DI)
unnamed: LOCK.DIN (DI), RANDSONG.DOUT (DO)
unnamed: GRAVE.DIN (DI), M5.DOUT (DO)
unnamed: 1.DIN (DI), GRAVE.DOUT (DO)
unnamed: 1.DOUT (DO), 2.DIN (DI)
unnamed: 2.DOUT (DO), 3.DIN (DI)
unnamed: 3.DOUT (DO), 4.DIN (DI)
unnamed: 4.DOUT (DO), 5.DIN (DI)
unnamed: 5.DOUT (DO), 6.DIN (DI)
unnamed: 6.DOUT (DO), 7.DIN (DI)
unnamed: 7.DOUT (DO), 8.DIN (DI)
unnamed: 8.DOUT (DO), 9.DIN (DI)
unnamed: 0.DIN (DI), 9.DOUT (DO)
unnamed: 0.DOUT (DO), DASH.DIN (DI)
unnamed: DASH.DOUT (DO), EQUAL.DIN (DI)
unnamed: BACKSPACE.DOUT (DO), INSERT.DIN (DI)
unnamed: HOME.DIN (DI), INSERT.DOUT (DO)
unnamed: HOME.DOUT (DO), PGUP.DIN (DI)
unnamed: NUMLOCK.DIN (DI), PGUP.DOUT (DO)
unnamed: KP_SLASH.DIN (DI), NUMLOCK.DOUT (DO)
unnamed: KP_ASTERISK.DIN (DI), KP_SLASH.DOUT (DO)
unnamed: KP_ASTERISK.DOUT (DO), KP_DASH.DIN (DI)
unnamed: KP_DASH.DOUT (DO), UNDERSCORE.DIN (DI)
unnamed: M4.DOUT (DO), TAB.DIN (DI)
unnamed: Q.DIN (DI), TAB.DOUT (DO)
unnamed: Q.DOUT (DO), W.DIN (DI)
unnamed: E.DIN (DI), W.DOUT (DO)
unnamed: E.DOUT (DO), R.DIN (DI)
unnamed: R.DOUT (DO), T.DIN (DI)
unnamed: T.DOUT (DO), Y.DIN (DI)
unnamed: U.DIN (DI), Y.DOUT (DO)
unnamed: I.DIN (DI), U.DOUT (DO)
unnamed: I.DOUT (DO), O.DIN (DI)
unnamed: O.DOUT (DO), P.DIN (DI)
unnamed: LBRACKET.DIN (DI), P.DOUT (DO)
unnamed: LBRACKET.DOUT (DO), RBRACKET.DIN (DI)
unnamed: BACKSLASH.DIN (DI), RBRACKET.DOUT (DO)
unnamed: BACKSLASH.DOUT (DO), DELETE.DIN (DI)
unnamed: DELETE.DOUT (DO), END.DIN (DI)
unnamed: END.DOUT (DO), PGDN.DIN (DI)
unnamed: KP_7.DIN (DI), PGDN.DOUT (DO)
unnamed: KP_7.DOUT (DO), KP_8.DIN (DI)
unnamed: KP_8.DOUT (DO), KP_9.DIN (DI)
unnamed: KP_9.DOUT (DO), PLUS2.VSS (DI)
unnamed: KP_5.DIN (DI), PLUS2.DIN (DO)
unnamed: CAPSLOCK.DIN (DI), M3.DOUT (DO)
unnamed: A.DIN (DI), CAPSLOCK.DOUT (DO)
unnamed: A.DOUT (DO), S.DIN (DI)
unnamed: D.DIN (DI), S.DOUT (DO)
unnamed: D.DOUT (DO), F.DIN (DI)
unnamed: F.DOUT (DO), G.DIN (DI)
unnamed: G.DOUT (DO), H.DIN (DI)
unnamed: H.DOUT (DO), J.DIN (DI)
unnamed: J.DOUT (DO), K.DIN (DI)
unnamed: K.DOUT (DO), L.DIN (DI)
unnamed: L.DOUT (DO), SEMICOLON.DIN (DI)
unnamed: QUOTE.DIN (DI), SEMICOLON.DOUT (DO)
unnamed: ENTER.DIN (DI), QUOTE.DOUT (DO)
unnamed: ENTER.DOUT (DO), KP_4.DIN (DI)
unnamed: ENTER2.VSS (DI), KP_3.DOUT (DO)
unnamed: KP_4.DOUT (DO), KP_52.DIN (DI)
unnamed: KP_6.DIN (DI), KP_52.DOUT (DO)
unnamed: KP_6.DOUT (DO), KP_62.DIN (DI)
unnamed: M2.DOUT (DO), SHIFT.DIN (DI)
unnamed: SHIFT.DOUT (DO), Z.DIN (DI)
unnamed: X.DIN (DI), Z.DOUT (DO)
unnamed: C.DIN (DI), X.DOUT (DO)
unnamed: C.DOUT (DO), V.DIN (DI)
unnamed: B.DIN (DI), V.DOUT (DO)
unnamed: B.DOUT (DO), N.DIN (DI)
unnamed: M.DIN (DI), N.DOUT (DO)
unnamed: COMMA.DIN (DI), M.DOUT (DO)
unnamed: COMMA.DOUT (DO), PERIOD.DIN (DI)
unnamed: PERIOD.DOUT (DO), SLASH.DIN (DI)
unnamed: SHIFT2.DIN (DI), SLASH.DOUT (DO)
unnamed: KP_1.DOUT (DO), KP_2.DIN (DI)
unnamed: KP_2.DOUT (DO), KP_3.DIN (DI)
unnamed: ENTER2.DIN (DO), KP_DELETE2.DIN (DI)
unnamed: KP_1.DIN (DI), SHIFT2.DOUT (DO)
unnamed: CTRL.DIN (DI), CTRL1.DOUT (DO)
unnamed: CTRL.DOUT (DO), WIN.DIN (DI)
unnamed: ALT.DIN (DI), WIN.DOUT (DO)
unnamed: ALT.DOUT (DO), SPACE.VSS (DI)
unnamed: ALT2.DIN (DI), SPACE.DOUT (DO)
unnamed: ALT2.DOUT (DO), WIN2.DIN (DI)
unnamed: MENU.DIN (DI), WIN2.DOUT (DO)
unnamed: CTRL2.DIN (DI), MENU.DOUT (DO)
unnamed: CTRL2.DOUT (DO), LEFT.DIN (DI)
unnamed: KP_0.DOUT (DO), KP_DEL.DIN (DI)
unnamed: BACKSPACE_1.DIN (DI), KP_DEL.DOUT (DO)
unnamed: DOWN.DIN (DI), LEFT.DOUT (DO)
unnamed: DOWN.DOUT (DO), RIGHT.DIN (DI)
ROW1: DBACKSONG.C, DESC.C, DF1.C, DF2.C, DF3.C, DF4.C, DF5.C, DF6.C, DF7.C, DF8.C, DF9.C, DF10.C, DF11.C, DF12.C, DLOCK.C, DM6.C, DNEXTSONG.C, DNEXTSONG1.C, DPAUSE.C, DPAUSEPLAY.C, DPRTSC.C, DSCROLLLOCK.C, DVOLUMEUP.C, DVOLUMNEDOWN.C; also elsewhere on the board
ROW2: D0.C, D1.C, D2.C, D3.C, D4.C, D5.C, D6.C, D7.C, D8.C, D9.C, DBACKSPACE.C, DDASH.C, DEQUAL.C, DGRAVE.C, DHOME.C, DINSERT.C, DKP_ASTERISK.C, DKP_DASH.C, DKP_SLASH.C, DM5.C, DNUMLOCK.C, DPGUP.C, DUNDERSCORE.C; also elsewhere on the board
ROW3: DBACKSLASH.C, DDELETE.C, DE.C, DEND.C, DEQUAL2.C, DI.C, DKP_5.C, DKP_7.C, DKP_8.C, DKP_9.C, DLBRACKET.C, DM4.C, DO.C, DP.C, DPGDN.C, DQ.C, DR.C, DRBRACKET.C, DT.C, DTAB.C, DU.C, DW.C, DY.C; also elsewhere on the board
ROW4: DA.C, DCAPSLOCK.C, DD.C, DENTER.C, DF.C, DG.C, DH.C, DJ.C, DK.C, DKP_4.C, DKP_6.C, DKP_52.C, DKP_62.C, DL.C, DM3.C, DQUOTE.C, DS.C, DSEMICOLON.C; also elsewhere on the board
ROW5: DB.C, DC.C, DCOMMA.C, DDELETE2.C, DENTER2.C, DKP_1.C, DKP_2.C, DKP_3.C, DM.C, DM2.C, DN.C, DPERIOD.C, DSHIFT.C, DSHIFT2.C, DSLASH.C, DUP.C, DV.C, DX.C, DZ.C; also elsewhere on the board
ROW6: DALT.C, DALT2.C, DBACKSPACE_1.C, DCTRL.C, DCTRL2.C, DDOWN.C, DKP_0.C, DKP_DEL.C, DLEFT.C, DM1.C, DMENU.C, DRIGHT.C, DSPACE.C, DWIN.C, DWIN2.C; also elsewhere on the board

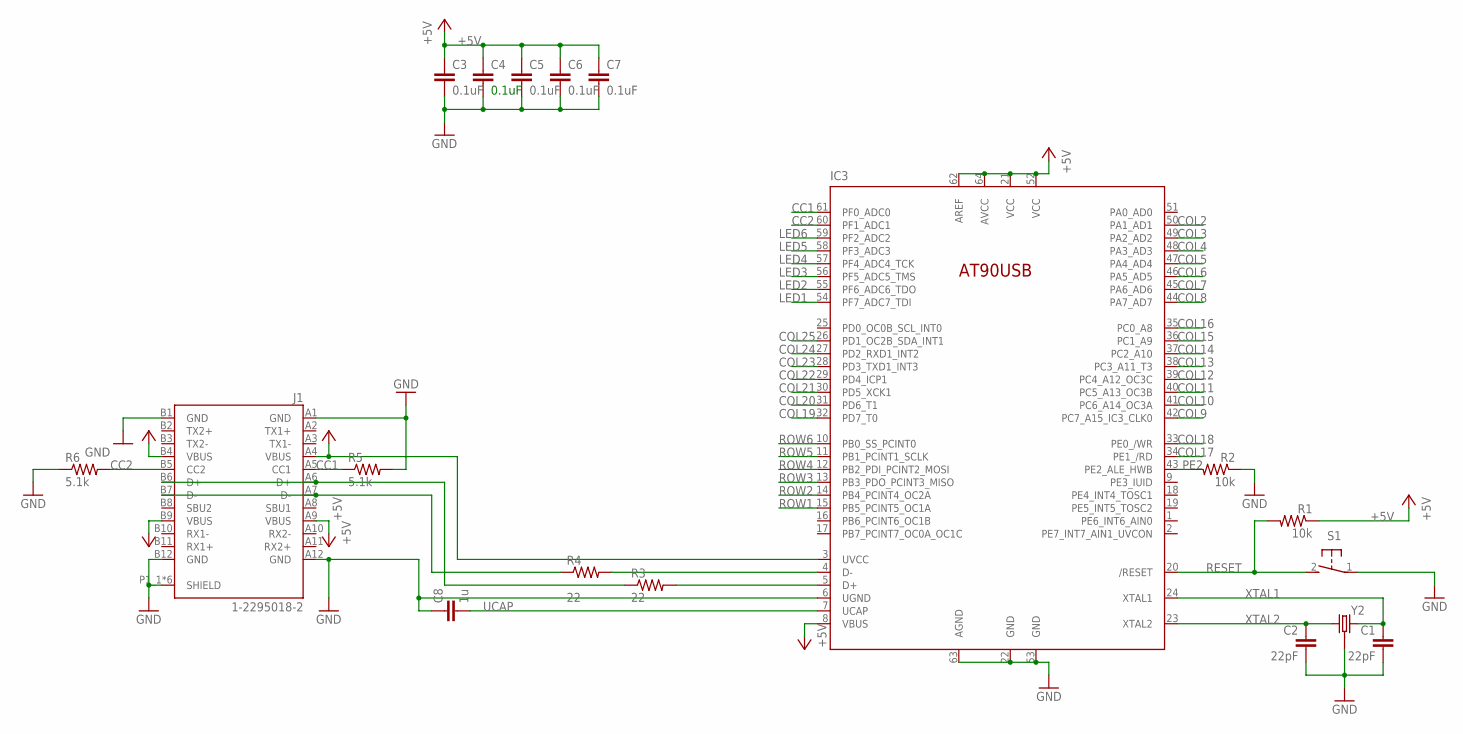
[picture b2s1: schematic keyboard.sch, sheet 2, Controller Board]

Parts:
C1, C2: 22pF; C0805
C3, C4, C5, C6, C7: 0.1uF; C0805
C8: 1u; C0805
IC3: AT90USB-TQFP; TQFP64
J1: 1-2295018-2; TE_1-2295018-2
R1, R2: 10k; M0805
R3, R4: 22; M0805
R5, R6: 5.1k; M0805
S1: 31-XX; B3F-31XX
Y2: CRYSTAL-GROUNDEDSMD-3.2X2.5; CRYSTAL-SMD-3.2X2.5MM

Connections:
+5V: C3.1, C4.1, C5.1, C6.1, C7.1, IC3.3 (UVCC), IC3.8 (VBUS), IC3.21 (VCC), IC3.52 (VCC), IC3.62 (AREF), IC3.64 (AVCC), J1.A4 (VBUS), J1.A9 (VBUS), J1.B4 (VBUS), J1.B9 (VBUS), R1.1; also elsewhere on the board
CC1: IC3.61 (PF0_ADC0), J1.A5 (CC1), R5.1
CC2: IC3.60 (PF1_ADC1), J1.B5 (CC2), R6.2
COL2: IC3.50 (PA1_AD1); also elsewhere on the board
COL3: IC3.49 (PA2_AD2); also elsewhere on the board
COL4: IC3.48 (PA3_AD3); also elsewhere on the board
COL5: IC3.47 (PA4_AD4); also elsewhere on the board
COL6: IC3.46 (PA5_AD5); also elsewhere on the board
COL7: IC3.45 (PA6_AD6); also elsewhere on the board
COL8: IC3.44 (PA7_AD7); also elsewhere on the board
COL9: IC3.42 (PC7_A15_IC3_CLK0); also elsewhere on the board
COL10: IC3.41 (PC6_A14_OC3A); also elsewhere on the board
COL11: IC3.40 (PC5_A13_OC3B); also elsewhere on the board
COL12: IC3.39 (PC4_A12_OC3C); also elsewhere on the board
COL13: IC3.38 (PC3_A11_T3); also elsewhere on the board
COL14: IC3.37 (PC2_A10); also elsewhere on the board
COL15: IC3.36 (PC1_A9); also elsewhere on the board
COL16: IC3.35 (PC0_A8); also elsewhere on the board
COL17: IC3.34 (PE1_/RD); also elsewhere on the board
COL18: IC3.33 (PE0_/WR); also elsewhere on the board
COL19: IC3.32 (PD7_T0); also elsewhere on the board
COL20: IC3.31 (PD6_T1); also elsewhere on the board
COL21: IC3.30 (PD5_XCK1); also elsewhere on the board
COL22: IC3.29 (PD4_ICP1); also elsewhere on the board
COL23: IC3.28 (PD3_TXD1_INT3); also elsewhere on the board
COL24: IC3.27 (PD2_RXD1_INT2); also elsewhere on the board
COL25: IC3.26 (PD1_OC2B_SDA_INT1); also elsewhere on the board
D+32U: IC3.5 (D+), R3.2
D+USB: J1.A6 (D+), J1.B6 (D+), R3.1
D-32U4: IC3.4 (D-), R4.2
D-USB: J1.A7 (D-), J1.B7 (D-), R4.1
GND: C1.2, C2.2, C3.2, C4.2, C5.2, C6.2, C7.2, C8.1, IC3.6 (UGND), IC3.22 (GND), IC3.53 (GND), IC3.63 (AGND), J1.A1 (GND), J1.A12 (GND), J1.B1 (GND), J1.B12 (GND), J1.P1_1 (SHIELD), J1.P1_2 (SHIELD), J1.P2_1 (SHIELD), J1.P2_2 (SHIELD), J1.P4 (SHIELD), J1.P5 (SHIELD), R2.1, R5.2, R6.1, S1.1, Y2.2 (3), Y2.4 (3); also elsewhere on the board
LED1: IC3.54 (PF7_ADC7_TDI); also elsewhere on the board
LED2: IC3.55 (PF6_ADC6_TDO); also elsewhere on the board
LED3: IC3.56 (PF5_ADC5_TMS); also elsewhere on the board
LED4: IC3.57 (PF4_ADC4_TCK); also elsewhere on the board
LED5: IC3.58 (PF3_ADC3); also elsewhere on the board
LED6: IC3.59 (PF2_ADC2); also elsewhere on the board
PE2: IC3.43 (PE2_ALE_HWB), R2.2
RESET: IC3.20 (/RESET), R1.2, S1.2 (S)
ROW1: IC3.15 (PB5_PCINT5_OC1A); also elsewhere on the board
ROW2: IC3.14 (PB4_PCINT4_OC2A); also elsewhere on the board
ROW3: IC3.13 (PB3_PDO_PCINT3_MISO); also elsewhere on the board
ROW4: IC3.12 (PB2_PDI_PCINT2_MOSI); also elsewhere on the board
ROW5: IC3.11 (PB1_PCINT1_SCLK); also elsewhere on the board
ROW6: IC3.10 (PB0_SS_PCINT0); also elsewhere on the board
UCAP: C8.2, IC3.7 (UCAP)
XTAL1: C1.1, IC3.24 (XTAL1), Y2.1
XTAL2: C2.1, IC3.23 (XTAL2), Y2.3 (2)

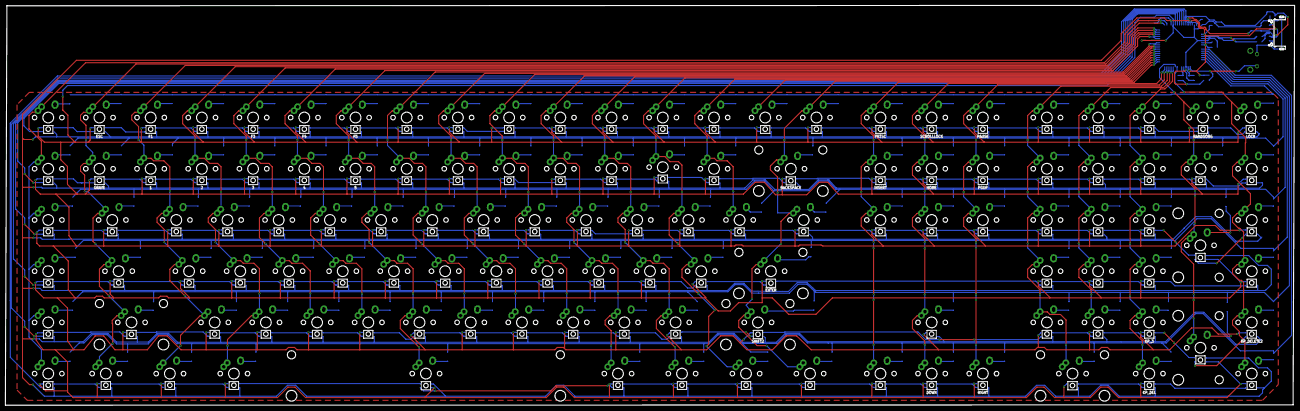
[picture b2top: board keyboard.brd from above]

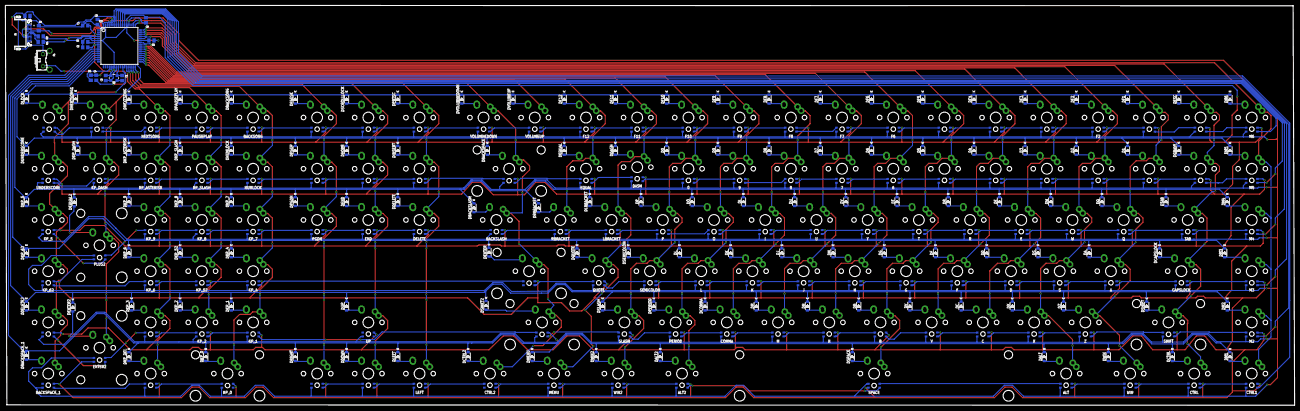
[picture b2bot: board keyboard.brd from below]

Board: 2 copper layers, 479.6 x 148.7 mm, 262 parts (140 on the bottom side), 285 nets.

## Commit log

2020-04-30 Started Eagle
2020-04-30 Added Scripts
2020-04-30 Added parts
2020-05-02 Updated Schematic
2020-05-02 Final Revision on positioning
2020-05-03 Fixed Board
2020-05-03 Updated alot and am having fun
2020-05-03 Added images
2020-05-03 Fixed Keys and added boardpng
2020-05-03 Updated Schematic Names
2020-05-04 Changed MCU to a larger chip
2020-05-05 Updated Schematics and boards
2020-05-05 Updated board
2020-05-05 Updated Schematic and rerouted board
2020-05-07 Thing
2020-05-08 Updated keyboard schematic. Slowely making progress
2020-05-08 Updated before rework of keys
2020-05-08 blank reverse
2020-05-20 Updated alot might switch to kicad
2020-05-21 Begining V2
2020-05-26 Updated Board with matrix
2020-05-27 Added Initial Routing
2020-05-30 Finished general key routing.
2020-05-31 Updated Board with power and gnd for leds
